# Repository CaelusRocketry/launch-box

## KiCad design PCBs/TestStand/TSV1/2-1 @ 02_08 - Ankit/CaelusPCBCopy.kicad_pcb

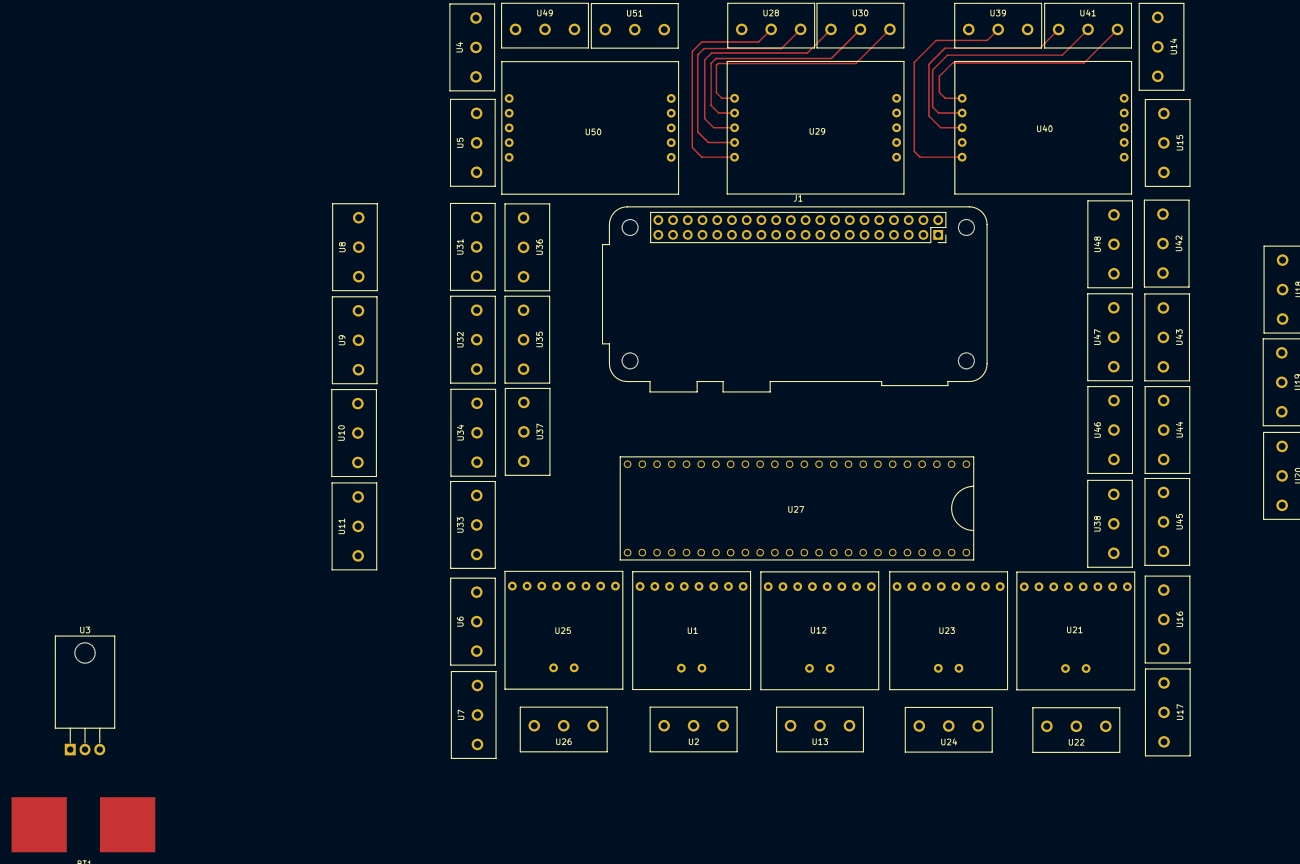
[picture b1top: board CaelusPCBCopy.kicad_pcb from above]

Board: 2 copper layers, 53 parts (0 on the bottom side), 65 nets.

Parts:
BT1: Battery_Cell; Lipo_Battery_Connector
J1: Raspberry_Pi_2_3; Raspberry_Pi_Zero_Socketed_THT_FaceDown_MountingHoles
U1, U12, U21, U23, U25: MAX31850
U2, U4, U5, U6, U7, U8, U9, U10, U11, U13, U14, U15, U16, U17, U18, U19, U20, U22, U24, U26, U28, U30, U31, U32, U33, U34, U35, U36, U37, U38, U39, U41, U42, U43, U44, U45, U46, U47, U48, U49, U51: SerialScrewTerminals; ScrewTerminals
U3: L7805; TO-220-3_Horizontal_TabDown
U27: Teensy3.6; Teensy 3.6
U29, U40, U50: LoadCellAmp

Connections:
1: U4.1, U27.1
2: U5.1, U27.2
3: U6.1, U27.3
4: U7.1, U27.4
5: U8.1, U27.5
6: U9.1, U27.6
7: U14.1, U27.7
8: U15.1, U27.8
9: U16.1, U27.9
10: U17.1, U27.10
11: U18.1, U27.11
12: U19.1, U27.12
13: U10.1, U27.24
14: U20.1, U27.25
15: U11.1, U27.26
16: U27.27, U29.8
17: U27.28, U29.7
18: U27.29, U40.8
19: U27.30, U40.7
20: U27.44, U50.8
21: U27.45, U50.7
+5V: J1.2, U1.2, U1.4, U1.6, U3.3, U4.2, U5.2, U6.2, U7.2, U8.2, U9.2, U10.2, U11.2, U12.2, U12.6, U14.2, U15.2, U16.2, U17.2, U18.2, U19.2, U20.2, U21.2, U21.4, U21.5, U23.2, U23.5, U25.2, U25.4, U27.40, U29.9, U29.10, U31.2, U32.2, U33.2, U34.2, U35.2, U36.2, U37.2, U38.2, U40.9, U40.10, U42.2, U43.2, U44.2, U45.2, U46.2, U47.2, U48.2, U50.9, U50.10
GND1: BT1.2, J1.6, J1.9, J1.14, J1.20, J1.25, J1.30, J1.34, J1.39, U1.1, U1.5, U1.7, U1.8, U3.2, U4.3, U5.3, U6.3, U7.3, U8.3, U9.3, U10.3, U11.3, U12.1, U12.4, U12.5, U12.7, U12.8, U14.3, U15.3, U16.3, U17.3, U18.3, U19.3, U20.3, U21.1, U21.6, U21.7, U21.8, U23.1, U23.4, U23.6, U23.7, U23.8, U25.1, U25.5, U25.6, U25.7, U25.8, U27.0, U27.46, U29.6, U31.3, U33.3, U34.3, U35.3, U36.3, U37.3, U38.3, U40.6, U42.3, U43.3, U44.3, U45.3, U46.3, U47.3, U48.3, U50.6
unnamed: BT1.1, U3.1
unnamed: J1.8, U27.31
unnamed: J1.10, U27.32
unnamed: U1.9, U2.1
unnamed: U1.10, U2.2
unnamed: U12.9, U13.1
unnamed: U12.10, U13.2
unnamed: U21.9, U22.1
unnamed: U21.10, U22.2
unnamed: U23.9, U24.1
unnamed: U23.10, U24.2
unnamed: U25.9, U26.1
unnamed: U25.10, U26.2
unnamed: U27.14, U46.1
unnamed: U27.15, U35.1
unnamed: U27.16, U45.1
unnamed: U27.17, U34.1
unnamed: U27.18, U44.1
unnamed: U27.19, U33.1
unnamed: U27.20, U43.1
unnamed: U27.21, U32.1
unnamed: U27.22, U42.1
unnamed: U27.23, U31.1
unnamed: U27.34, U38.1
unnamed: U27.35, U48.1
unnamed: U27.36, U37.1
unnamed: U27.37, U47.1
unnamed: U27.38, U36.1
unnamed: U28.1, U29.4
unnamed: U28.2, U29.5
unnamed: U29.1, U30.1
unnamed: U29.2, U30.2
unnamed: U29.3, U30.3
unnamed: U39.2, U40.5
unnamed: U40.1, U41.1
unnamed: U40.2, U41.2
unnamed: U40.3, U41.3
unnamed: U49.1, U50.4
unnamed: U49.2, U50.5
unnamed: U50.1, U51.1
unnamed: U50.2, U51.2
unnamed: U50.3, U51.3

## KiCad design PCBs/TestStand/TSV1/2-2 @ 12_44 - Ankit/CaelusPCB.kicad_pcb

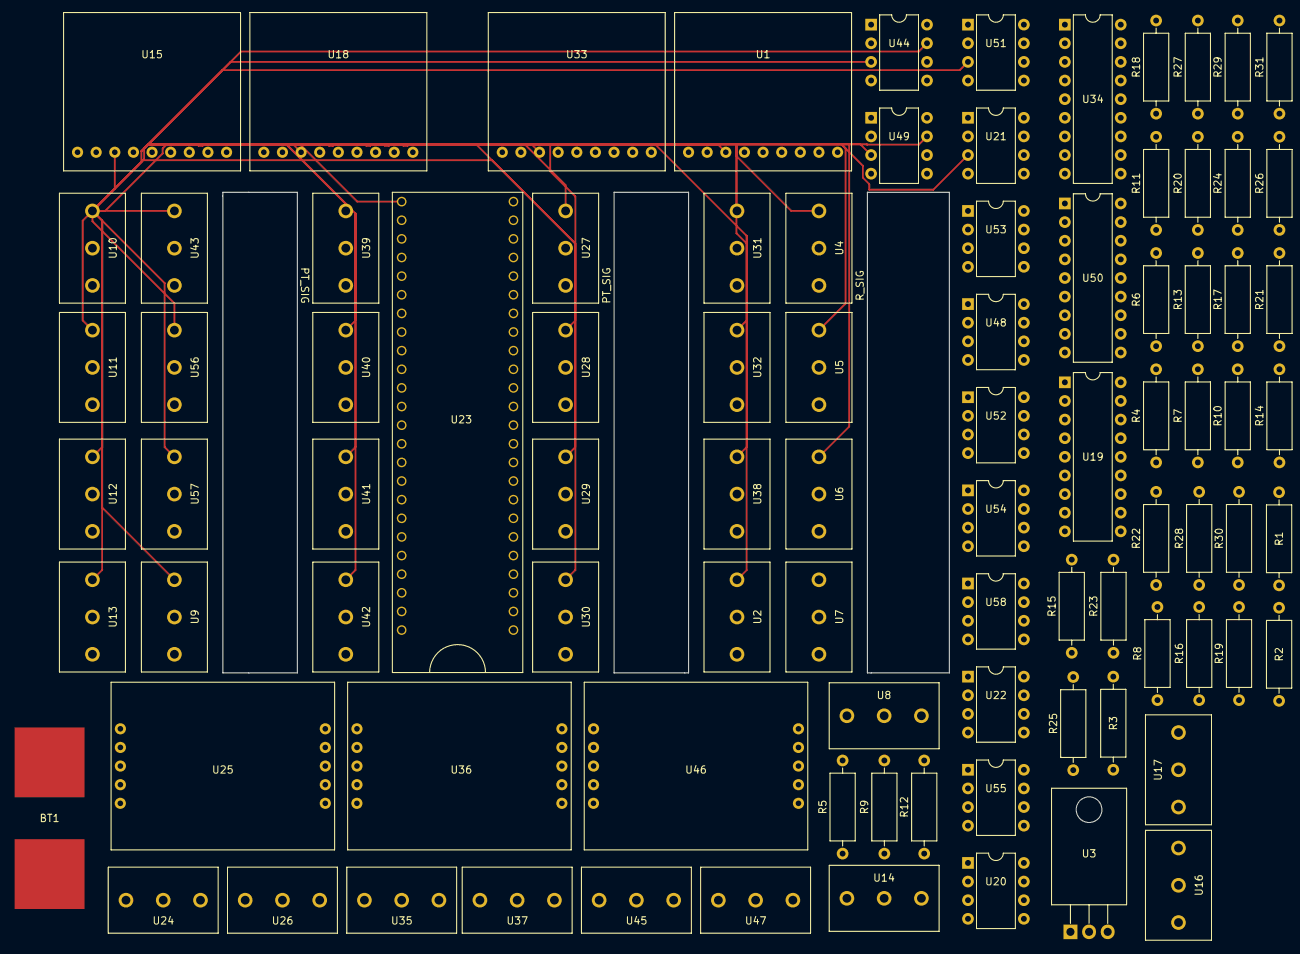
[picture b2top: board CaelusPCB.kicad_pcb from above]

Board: 2 copper layers, 90 parts (0 on the bottom side), 105 nets.

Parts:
BT1: Battery_Cell; Lipo_Battery_Connector
R1, R2, R3, R4, R5, R6, R7, R8, R9, R10, R11, R12, R13, R14, R15, R16, R17, R18, R19, R20, R21, R22, R23, R24, R25, R26, R27, R28, R29, R30, R31: R_US; R_Axial_DIN0309_L9.0mm_D3.2mm_P12.70mm_Horizontal
U1, U15, U18, U33: MAX31856
U2, U4, U5, U6, U7, U8, U9, U10, U11, U12, U13, U14, U16, U17, U24, U26, U27, U28, U29, U30, U31, U32, U35, U37, U38, U39, U40, U41, U42, U43, U45, U47, U56, U57: SerialScrewTerminals; ScrewTerminals
U3: L7805; TO-220-3_Horizontal_TabDown
U19, U34, U50: Launchbox_HT12D; DIP-18_W7.62mm
U20, U21, U22, U44, U48, U49, U51, U52, U53, U54, U55, U58: SPDT_IC; DIP-8_W7.62mm
U23: Teensy3.6; Teensy 3.6
U25, U36, U46: LoadCellAmp

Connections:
1: U1.4, U15.4, U18.4, U23.32, U33.4
2: U23.31, U33.7
3: U20.2, U23.3
4: U23.4, U44.2
5: U23.5, U51.2
6: U21.2, U23.6
7: U23.7, U48.2
8: U23.8, U52.2
9: U23.9, U54.2
10: U23.10, U58.2
11: U22.2, U23.11
12: U23.12, U49.2
13: U1.6, U15.6, U18.6, U23.0, U33.6
14: U1.5, U15.5, U18.5, U23.1, U33.5
15: U18.7, U23.2
16: U23.25, U25.8
17: U23.26, U25.7
18: U23.27, U36.8
19: U23.28, U36.7
20: U23.29, U46.8
21: U23.30, U46.7
25: U17.1, U50.14
26: U17.2, U34.14
27: U17.3, U19.14
28: U20.8, U50.13
29: U44.8, U50.12
30: U50.11, U51.8
31: U21.8, U50.10
32: U34.13, U48.8
33: U34.12, U52.8
34: U34.11, U54.8
35: U34.10, U58.8
36: U19.13, U22.8
37: U19.12, U49.8
38: U19.11, U53.8
39: U19.10, U55.8
40: U2.1, U20.1
41: U4.1, U44.1
42: U5.1, U51.1
43: U6.1, U21.1
44: U7.1, U48.1
45: U8.1, U52.1
46: U12.1, U54.1
47: U13.1, U58.1
48: U11.1, U22.1
49: U14.1, U49.1
50: U15.7, U23.33
51: U1.7, U23.34
52: U16.1, U20.6, U21.6, U22.6, U44.6, U48.6, U49.6, U51.6, U52.6, U53.6, U54.6, U55.6, U58.6
53: U9.1, U53.1
54: U10.1, U55.1
55: R10.2, R17.1, U23.36
56: R18.2, R25.1, U23.39
57: U23.13, U53.2
58: U23.35, U55.2
+5V: U1.1, U2.2, U3.3, U4.2, U5.2, U6.2, U7.2, U8.2, U9.2, U10.2, U11.2, U12.2, U13.2, U14.2, U15.1, U18.1, U19.17, U19.18, U20.4, U20.5, U21.4, U21.5, U22.4, U22.5, U23.40, U25.9, U25.10, U27.2, U28.2, U29.2, U30.2, U31.2, U32.2, U33.1, U34.17, U34.18, U36.9, U36.10, U38.2, U39.2, U40.2, U41.2, U42.2, U43.2, U44.4, U44.5, U46.9, U46.10, U48.4, U48.5, U49.4, U49.5, U50.17, U50.18, U51.4, U51.5, U52.4, U52.5, U53.4, U53.5, U54.4, U54.5, U55.4, U55.5, U56.2, U57.2, U58.4, U58.5
GND1: BT1.2, R4.1, R5.1, R6.1, R7.1, R8.1, R9.1, R10.1, R25.2, R26.2, R27.2, R28.2, R29.2, R30.2, R31.2, U1.3, U2.3, U3.2, U4.3, U5.3, U6.3, U7.3, U8.3, U9.3, U10.3, U11.3, U12.3, U13.3, U14.3, U15.3, U16.2, U18.3, U19.1, U19.2, U19.3, U19.4, U19.5, U19.6, U19.7, U19.8, U19.9, U20.3, U20.7, U21.3, U21.7, U22.3, U22.7, U23.46, U25.6, U27.3, U28.3, U29.3, U30.3, U31.3, U32.3, U33.3, U34.1, U34.2, U34.3, U34.4, U34.5, U34.6, U34.7, U34.8, U34.9, U36.6, U38.3, U39.3, U40.3, U41.3, U42.3, U43.3, U44.3, U44.7, U46.6, U48.3, U48.7, U49.3, U49.7, U50.1, U50.2, U50.3, U50.4, U50.5, U50.6, U50.7, U50.8, U50.9, U51.3, U51.7, U52.3, U52.7, U53.3, U53.7, U54.3, U54.7, U55.3, U55.7, U56.3, U57.3, U58.3, U58.7
unnamed: BT1.1, U3.1
unnamed: R1.1, U19.16
unnamed: R1.2, U19.15
unnamed: R2.1, U34.16
unnamed: R2.2, U34.15
unnamed: R3.1, U50.16
unnamed: R3.2, U50.15
unnamed: R7.2, R11.1, U23.21
unnamed: R11.2, U28.1
unnamed: R4.2, R12.1, U23.19
unnamed: R12.2, U29.1
unnamed: R5.2, R13.1, U23.17
unnamed: R13.2, U30.1
unnamed: R8.2, R14.1, U23.38
unnamed: R14.2, U32.1
unnamed: R6.2, R15.1, U23.23
unnamed: R15.2, U27.1
unnamed: R9.2, R16.1, U23.15
unnamed: R16.2, U31.1
unnamed: R17.2, U56.1
unnamed: R18.1, U57.1
unnamed: R19.1, U38.1
unnamed: R19.2, R26.1, U23.22
unnamed: R20.1, U39.1
unnamed: R20.2, R27.1, U23.20
unnamed: R21.1, U40.1
unnamed: R21.2, R28.1, U23.18
unnamed: R22.1, U41.1
unnamed: R22.2, R29.1, U23.16
unnamed: R23.1, U42.1
unnamed: R23.2, R30.1, U23.14
unnamed: R24.1, U43.1
unnamed: R24.2, R31.1, U23.37
unnamed: U24.1, U25.4
unnamed: U24.2, U25.5
unnamed: U25.1, U26.1
unnamed: U25.2, U26.2
unnamed: U25.3, U26.3
unnamed: U35.1, U36.4
unnamed: U35.2, U36.5
unnamed: U36.1, U37.1
unnamed: U36.2, U37.2
unnamed: U36.3, U37.3
unnamed: U45.1, U46.4
unnamed: U45.2, U46.5
unnamed: U46.1, U47.1
unnamed: U46.2, U47.2
unnamed: U46.3, U47.3
